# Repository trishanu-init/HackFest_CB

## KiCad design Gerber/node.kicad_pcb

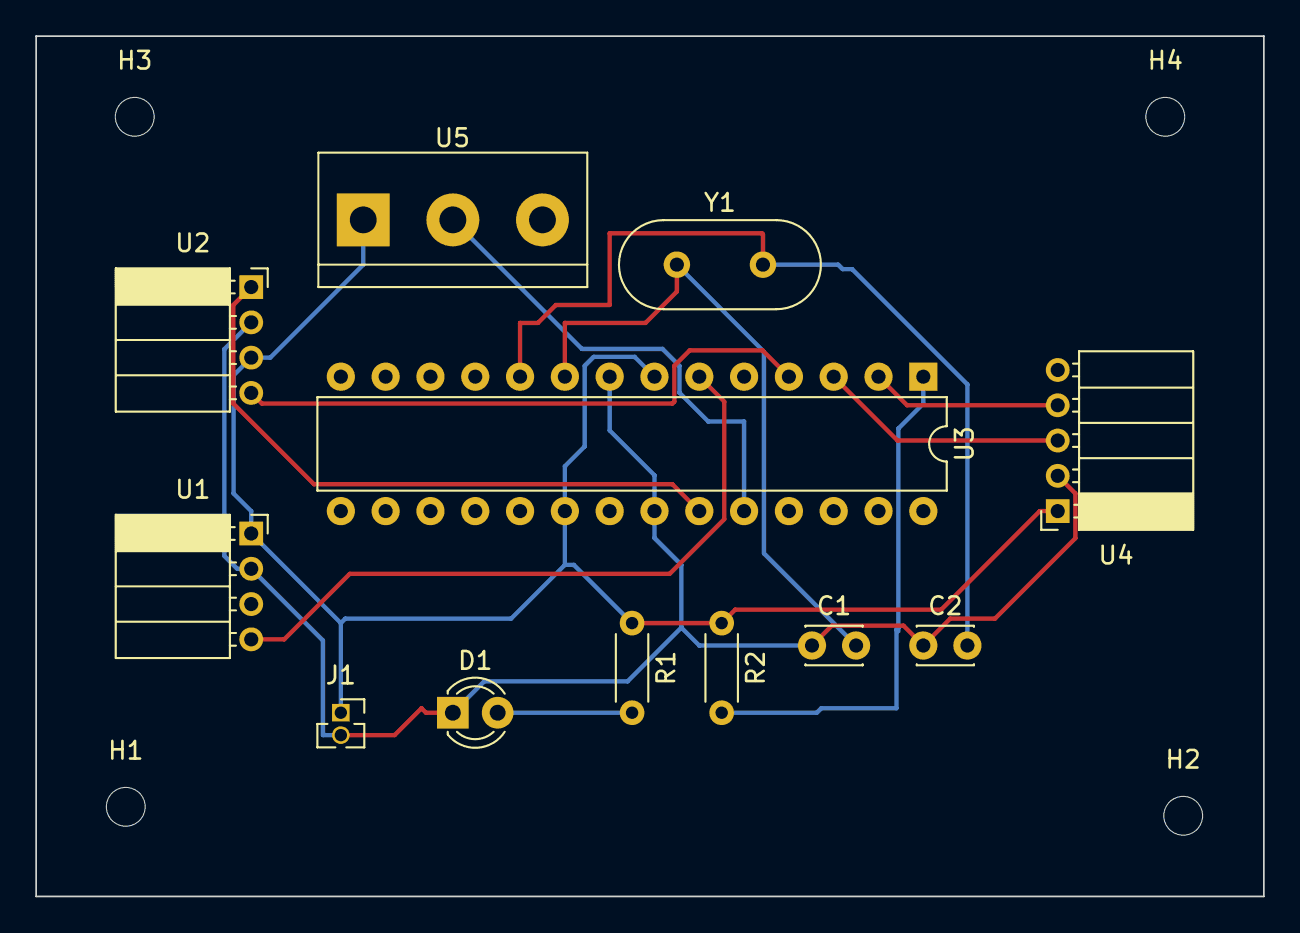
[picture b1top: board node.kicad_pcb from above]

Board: 2 copper layers, 69.6 x 48.8 mm, 16 parts (0 on the bottom side), 12 nets.

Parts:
C1, C2: C; C_Disc_D3.0mm_W2.0mm_P2.50mm
D1: LED; LED_D3.0mm
H1, H2, H3, H4: MountingHole; MountingHole_2.2mm_M2
J1: Conn_01x02_Female; PinSocket_1x02_P1.27mm_Vertical
R1, R2: R; R_Axial_DIN0204_L3.6mm_D1.6mm_P5.08mm_Horizontal
U1: MQ7; PinSocket_1x04_P2.00mm_Horizontal
U2: KY026; PinSocket_1x04_P2.00mm_Horizontal
U3: ATmega328-PU; DIP-28_W7.62mm
U4: HC-12; PinSocket_1x05_P2.00mm_Horizontal
U5: DHT11; TerminalBlock_bornier-3_P5.08mm
Y1: Crystal; Crystal_HC49-4H_Vertical

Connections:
+5V: J1.1, R1.1, R2.1, U1.1, U2.3, U3.7, U3.20, U4.1, U5.1
GND: C1.1, C2.1, D1.1, J1.2, U1.2, U2.2, U3.8, U3.22, U4.2
unnamed: C1.2, U3.9, Y1.1
unnamed: C2.2, U3.10, Y1.2
unnamed: D1.2, R1.2
unnamed: R2.2, U3.1
unnamed: U1.4, U3.6
unnamed: U2.1, U3.23
unnamed: U2.4, U3.4
unnamed: U3.2, U4.4
unnamed: U3.3, U4.3
unnamed: U3.24, U5.2

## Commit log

2023-06-10 uploaded files for about page
2023-06-11 added team images
2023-06-11 added social links
2023-06-27 Added dashboard files
2023-06-28 updated firebase config
2023-06-29 Changed firebase config
2023-06-29 Added INO files
2023-06-29 changed table caption
2023-06-29 changed navbar style
2023-06-30 Changed emergency.html
2023-06-30 changed delay time
2023-07-05 uploaded team imgs
2024-01-21 push to public cleanup
2024-01-27 added initial gerber files
2024-01-27 node kicad pcb file
2024-06-19 added members page
